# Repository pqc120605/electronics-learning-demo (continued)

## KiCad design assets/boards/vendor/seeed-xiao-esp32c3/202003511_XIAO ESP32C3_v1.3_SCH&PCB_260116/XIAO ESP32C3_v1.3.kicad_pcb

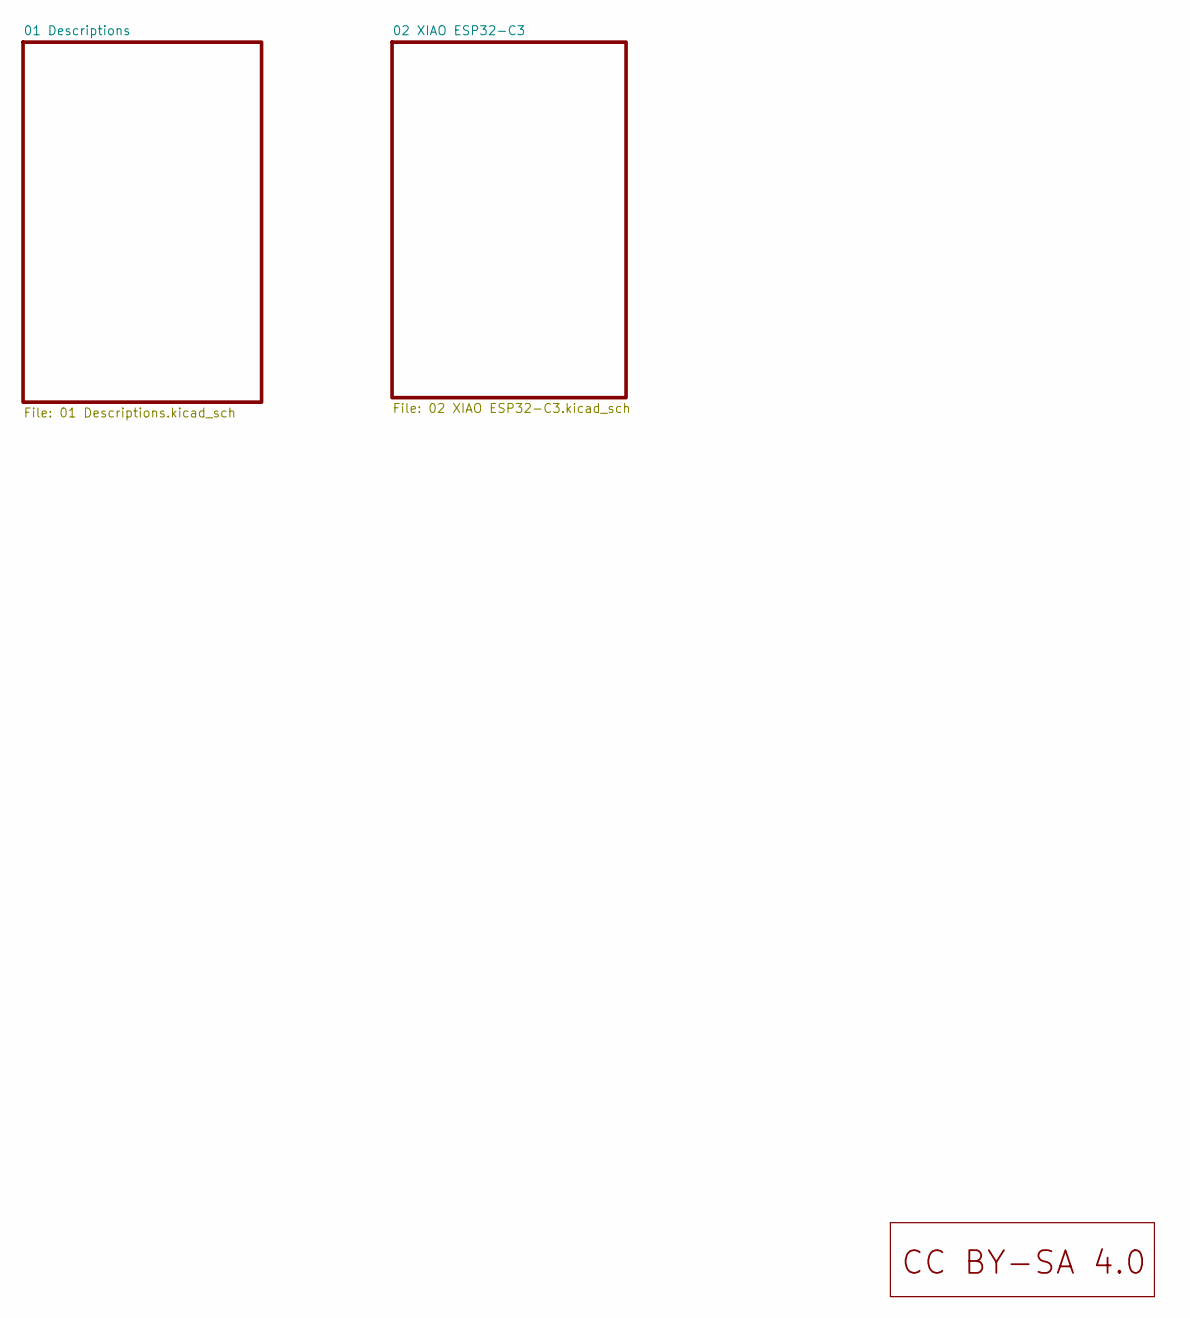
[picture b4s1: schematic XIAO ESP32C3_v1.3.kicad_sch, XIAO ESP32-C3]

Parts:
U3: LOGO_CC_BY-SA_4.0

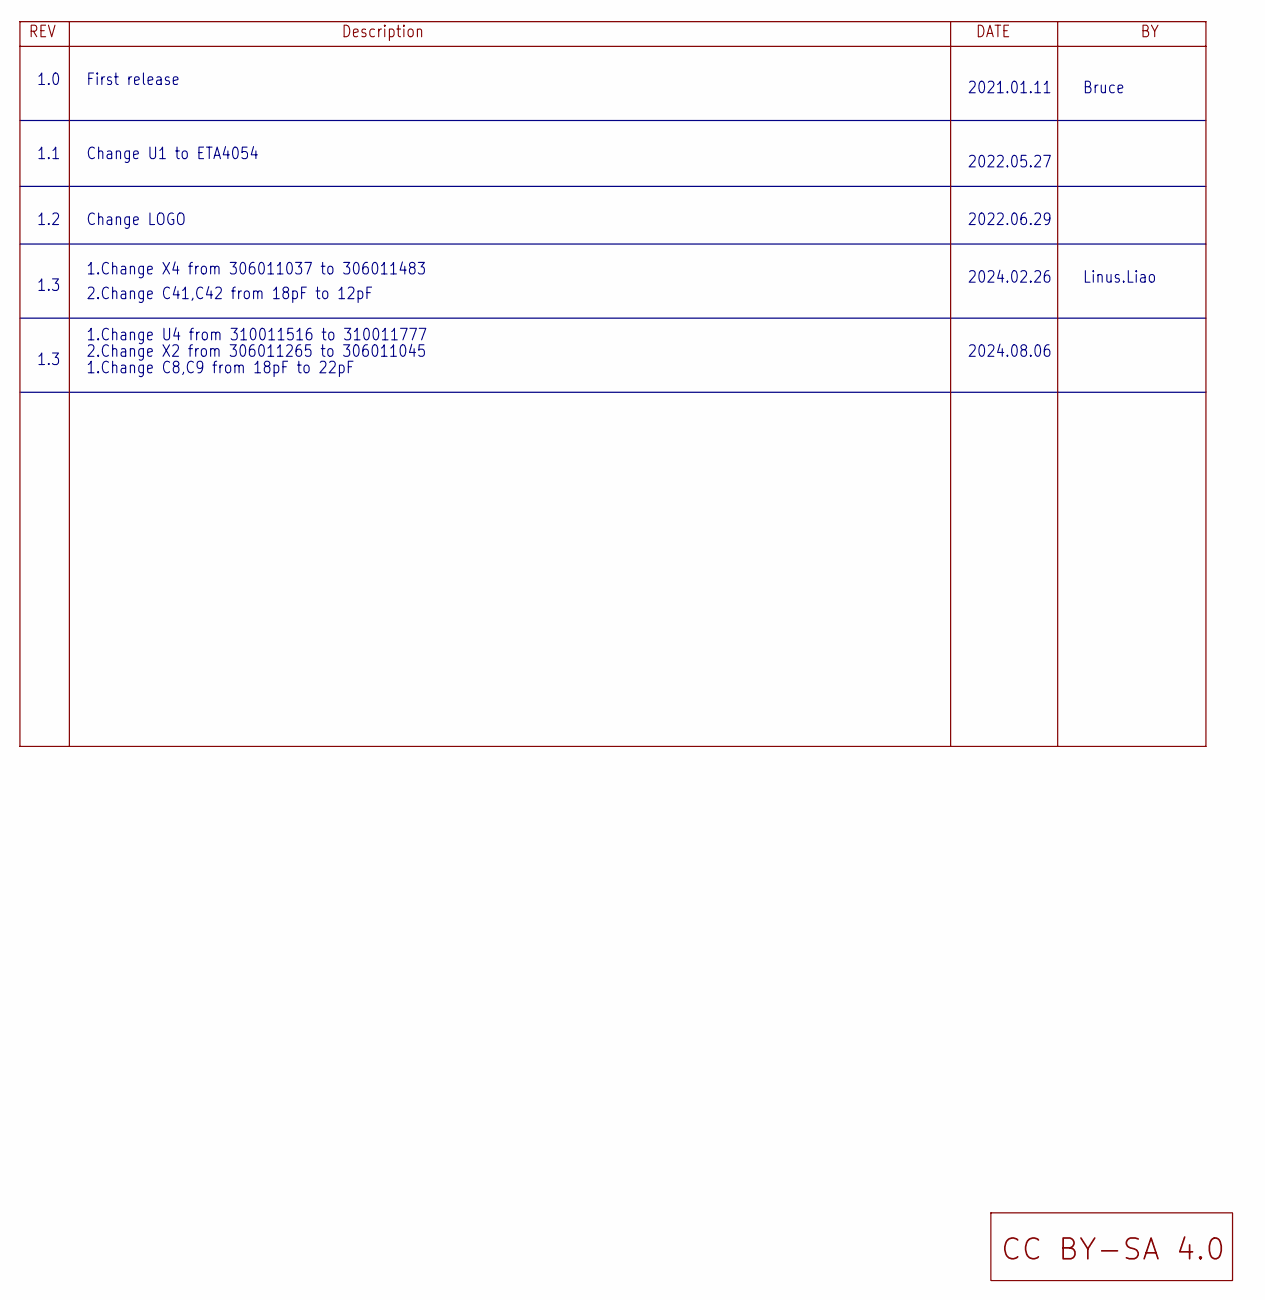
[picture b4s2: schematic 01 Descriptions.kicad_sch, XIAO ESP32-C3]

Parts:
U5: LOGO_CC_BY-SA_4.0

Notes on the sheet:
1.0
1.Change X4 from 306011037 to 306011483
1.Change U4 from 310011516 to 310011777
1.3
1.2
2.Change C41,C42 from 18pF to 12pF
2022.06.29
2022.05.27
Linus.Liao
2.Change X2 from 306011265 to 306011045
Bruce
2024.08.06
1.1
Change LOGO
2024.02.26
2021.01.11
First release
Change U1 to ETA4054
1.Change C8,C9 from 18pF to 22pF

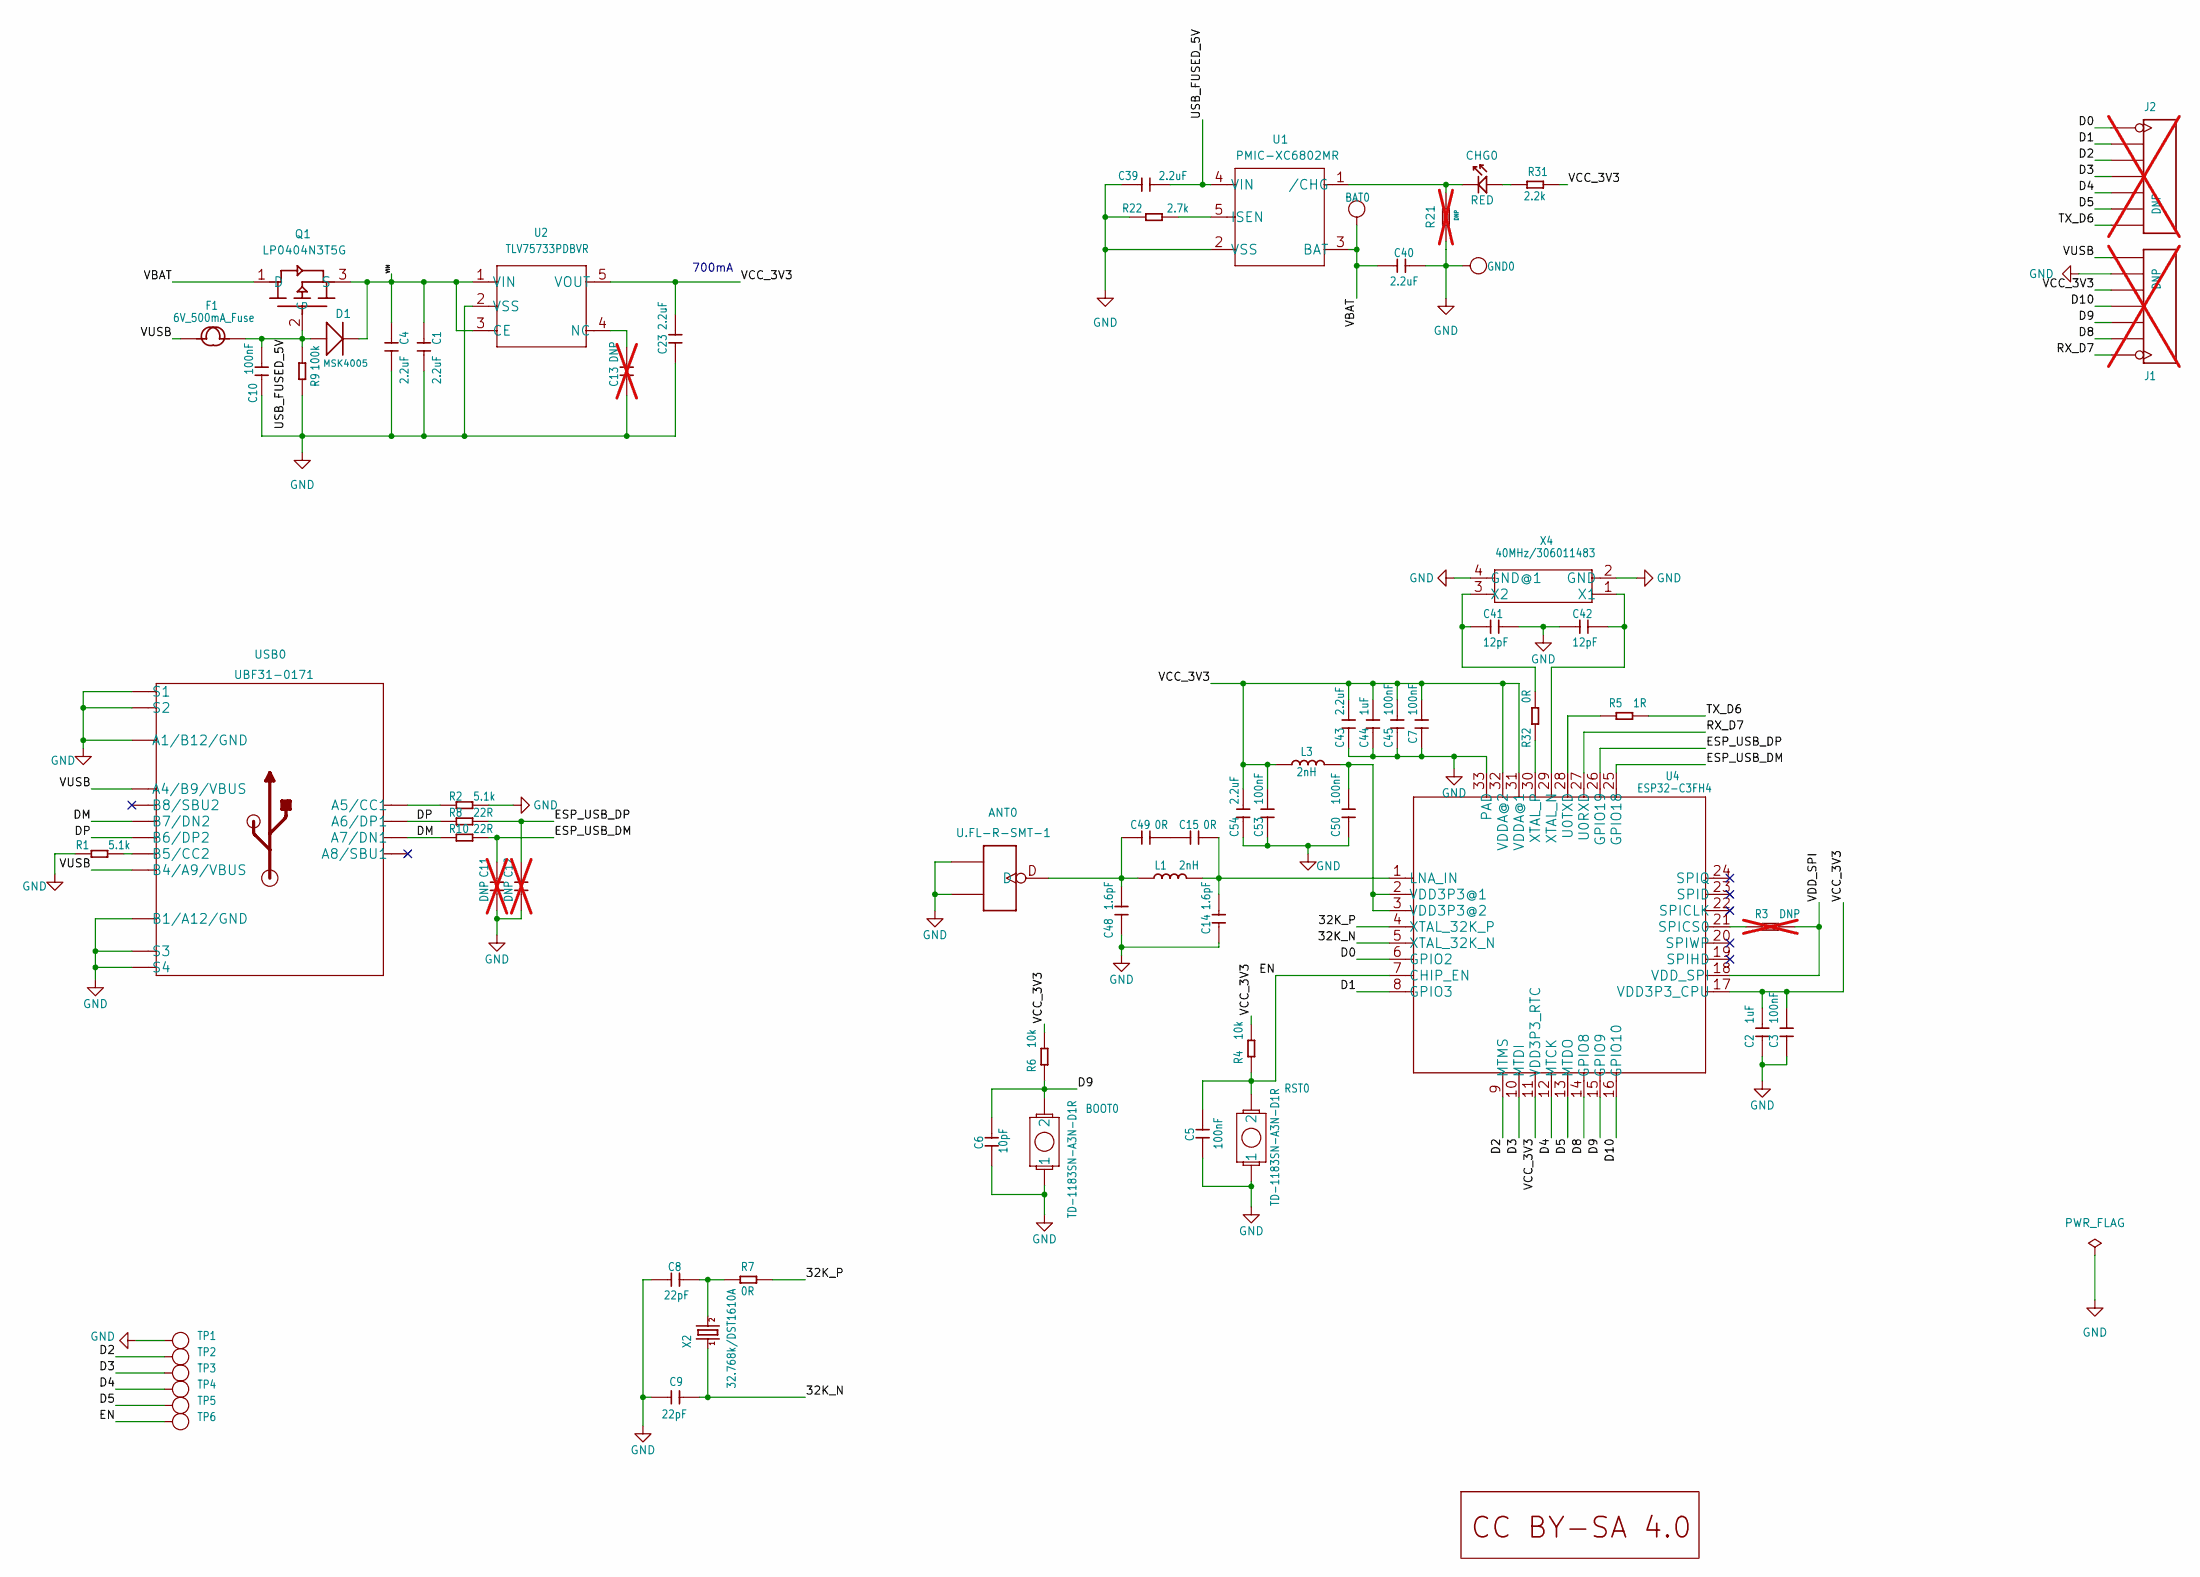
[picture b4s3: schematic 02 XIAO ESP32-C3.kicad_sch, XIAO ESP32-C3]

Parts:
ANT0: U.FL-R-SMT-1; U-FL3P-SMD-2.6X2.6X1.0MM
BAT0: DNP; TP-80X40MIL
BOOT0: TD-1183SN-A3N-D1R; BUTTON_TD1183SA
C1, C4, C23, C39, C40, C43, C54: 2.2uF; C0201
C2, C44: 1uF; C0201
C3, C5, C7, C10, C45, C50, C53: 100nF; C0201
C6: 10pF; C0201
C8, C9: 22pF; C0201
C11, C12, C13: DNP; C0201; not fitted
C14, C48: 1.6pF; C0201
C15, C49: 0R; C0201
C41, C42: 12pF; C0201
CHG0: RED; LED-0402
D1: MSK4005; SOD-523
F1: 6V_500mA_Fuse; F0603
GND0: DNP; TP-80X40MIL
J1, J2: DNP; H7-HALF-HOLE-2.54; not fitted
L1, L3: 2nH; L0201
Q1: LP0404N3T5G; PMOS_1.0_0.6_0.35MM
R1, R2: 5.1k; R0201
R3, R21: DNP; R0201; not fitted
R4, R6: 10k; R0201
R5: 1R; R0201
R7, R32: 0R; R0201
R8, R10: 22R; R0201
R9: 100k; R0201
R22: 2.7k; R0201
R31: 2.2k; R0201
RST0: TD-1183SN-A3N-D1R; BUTTON_TD1183SA
TP1, TP2, TP3, TP4, TP5, TP6: DNP; TP-D45MIL
U1: PMIC-XC6802MR; SOT-25
U2: TLV75733PDBVR; SOT-25
U4: ESP32-C3FH4; QFN32G-0.5-5X5MM
U6: LOGO_CC_BY-SA_4.0
USB0: UBF31-0171; USB2.0-TYPE-C
X2: 32.768k/DST1610A; X2-SMD-1.6X1.0X0.5MM
X4: 40MHz/306011483; X4-SMD-2.0X1.6X0.5MM

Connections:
32K_N: C9.1, U4.5 (XTAL_32K_N), X2.1
32K_P: R7.1, U4.4 (XTAL_32K_P)
D0: J2.1, J2.13 (1), U4.6 (GPIO2)
D1: J2.2, J2.14 (2), U4.8 (GPIO3)
D2: J2.3, J2.15 (3), TP2.T, U4.9 (MTMS)
D3: J2.4, J2.16 (4), TP3.T, U4.10 (MTDI)
D4: J2.5, J2.17 (5), TP4.T, U4.12 (MTCK)
D5: J2.6, J2.18 (6), TP5.T, U4.13 (MTDO)
D8: J1.2, J1.14 (2), U4.14 (GPIO8)
D9: BOOT0.2, C6.2, J1.3, J1.15 (3), R6.1, U4.15 (GPIO9)
D10: J1.4, J1.16 (4), U4.16 (GPIO10)
DM: R10.1, USB0.A7 (A7/DN1), USB0.B7 (B7/DN2)
DP: R8.1, USB0.A6 (A6/DP1), USB0.B6 (B6/DP2)
EN: C5.2, R4.1, RST0.2, TP6.T, U4.7 (CHIP_EN)
ESP_USB_DM: C11.2, R10.2, U4.25 (GPIO18)
ESP_USB_DP: C12.2, R8.2, U4.26 (GPIO19)
GND: ANT0.GND1, ANT0.GND2, BOOT0.1, C1.2, C2.1, C3.1, C4.2, C5.1, C6.1, C7.1, C8.2, C9.2, C10.1, C11.1, C12.1, C13.1, C14.1, C23.1, C39.1, C40.2, C41.2, C42.2, C43.1, C44.1, C45.1, C48.1, C50.1, C53.1, C54.1, GND0.1, J1.6, J1.18 (6), R1.1, R2.2, R9.1, R21.2, R22.2, RST0.1, TP1.T, U1.2 (VSS), U2.2 (VSS), U4.33 (PAD), USB0.A1_B12 (A1/B12/GND), USB0.B1_A12 (B1/A12/GND), USB0.S1, USB0.S2, USB0.S3, USB0.S4, USB0.S5 (S1), USB0.S6 (S2), X4.2 (GND), X4.4 (GND@1)
unnamed: R2.1, USB0.A5 (A5/CC1)
unnamed: R1.2, USB0.B5 (B5/CC2)
unnamed: R3.1, U4.21 (SPICS0)
unnamed: C8.1, R7.2, X2.2
unnamed: C13.2, U2.4 (NC)
unnamed: C15.2, C49.1
unnamed: R22.1, U1.5 (ISEN)
unnamed: CHG0.+, R31.2
unnamed: C14.2, C15.1, L1.2, U4.1 (LNA_IN)
unnamed: C41.1, R32.2, X4.3 (X2)
unnamed: C42.1, U4.29 (XTAL_N), X4.1 (X1)
unnamed: ANT0.D, C48.2, C49.2, L1.1
unnamed: R5.2, U4.28 (U0TXD)
unnamed: C50.2, L3.2, U4.2 (VDD3P3@1), U4.3 (VDD3P3@2)
unnamed: R32.1, U4.30 (XTAL_P)
RX_D7: J1.1, J1.13 (1), U4.27 (U0RXD)
TX_D6: J2.7, J2.19 (7), R5.1
USB_FUSED_5V: C10.2, C39.2, D1.+, F1.2, Q1.2 (G), R9.2, U1.4 (VIN)
VBAT: BAT0.1, C40.1, Q1.1 (D), U1.3 (BAT)
VCC_3V3: C2.2, C3.2, C7.2, C23.2, C43.2, C44.2, C45.2, C53.2, C54.2, J1.5, J1.17 (5), L3.1, R4.2, R6.2, R31.1, U2.5 (VOUT), U4.11 (VDD3P3_RTC), U4.17 (VDD3P3_CPU), U4.31 (VDDA@1), U4.32 (VDDA@2)
VDD_SPI: R3.2, U4.18 (VDD_SPI)
VIN: C1.1, C4.1, D1.-, Q1.3 (S), U2.1 (VIN), U2.3 (CE)
VUSB: F1.1, J1.7, J1.19 (7), USB0.A4_B9 (A4/B9/VBUS), USB0.B4_A9 (B4/A9/VBUS)
~CHG: CHG0.-, R21.1, U1.1 (/CHG)

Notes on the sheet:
700mA

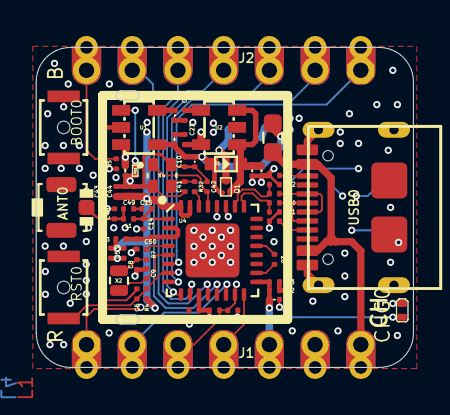
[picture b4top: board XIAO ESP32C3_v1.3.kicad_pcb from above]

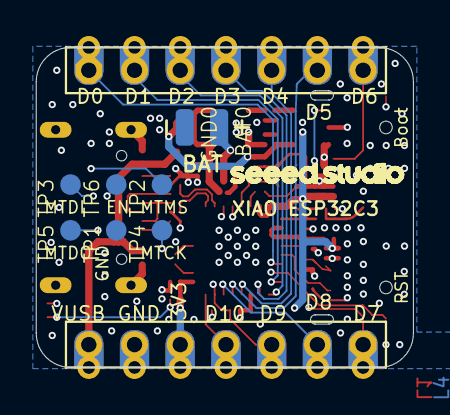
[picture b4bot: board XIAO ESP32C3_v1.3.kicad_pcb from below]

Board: 4 copper layers, 21.0 x 17.8 mm, 68 parts (9 on the bottom side), 41 nets.

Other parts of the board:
U$2: LOGO-SEEED-NEW-1X9.6MM
